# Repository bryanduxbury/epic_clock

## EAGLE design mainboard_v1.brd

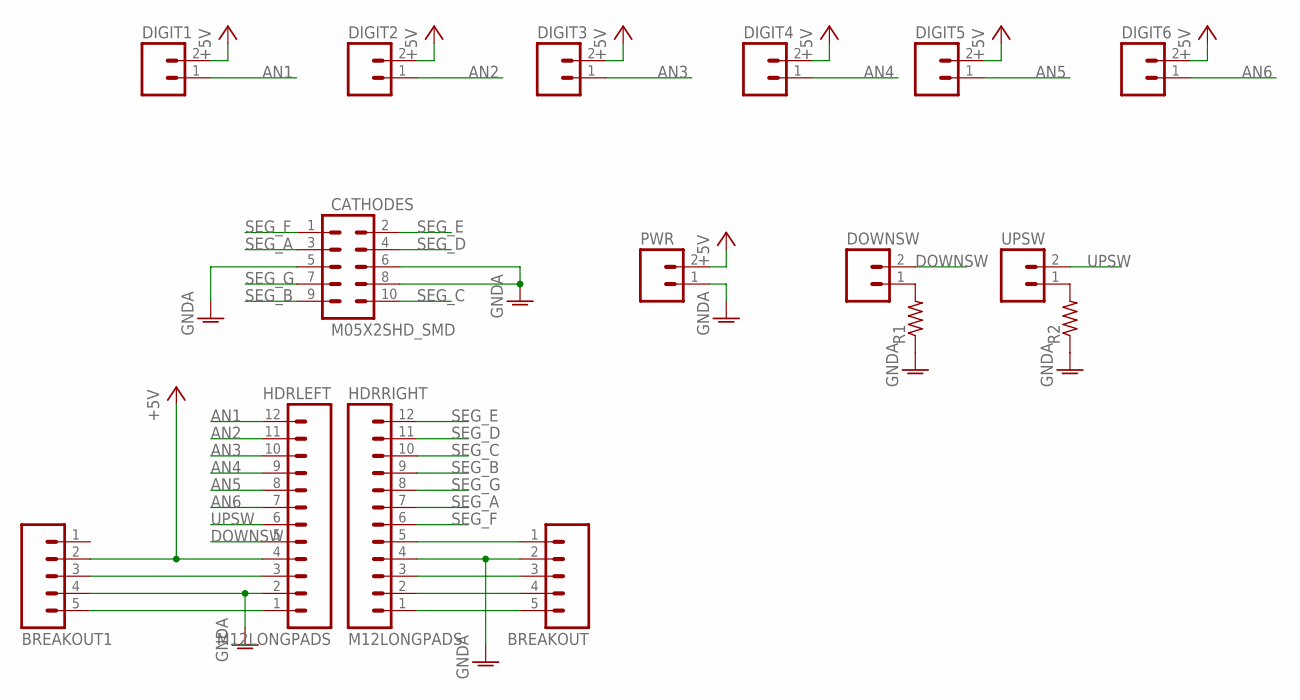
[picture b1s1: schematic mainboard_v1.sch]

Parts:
BREAKOUT, BREAKOUT1: M05; 05P
CATHODES: M05X2SHD_SMD; 2X5-SHROUDED_SMD
DIGIT1, DIGIT2, DIGIT3, DIGIT4, DIGIT5, DIGIT6: M02; 02P
DOWNSW: M02; 02P
HDRLEFT: M12LONGPADS; 1X12_LONGPADS
HDRRIGHT: M12LONGPADS; 1X12_LONGPADS
PWR: M02; 02P
R1, R2: R-US_M0805; M0805
UPSW: M02; 02P

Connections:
+5V: BREAKOUT1.2, DIGIT1.2, DIGIT2.2, DIGIT3.2, DIGIT4.2, DIGIT5.2, DIGIT6.2, HDRLEFT.4, PWR.2
AN1: DIGIT1.1, HDRLEFT.12
AN2: DIGIT2.1, HDRLEFT.11
AN3: DIGIT3.1, HDRLEFT.10
AN4: DIGIT4.1, HDRLEFT.9
AN5: DIGIT5.1, HDRLEFT.8
AN6: DIGIT6.1, HDRLEFT.7
DOWNSW: DOWNSW.2, HDRLEFT.5
GNDA: BREAKOUT.2, BREAKOUT1.4, CATHODES.5, CATHODES.6, CATHODES.8, HDRLEFT.2, HDRRIGHT.4, PWR.1, R1.1, R2.1
unnamed: DOWNSW.1, R1.2
unnamed: BREAKOUT.1, HDRRIGHT.5
unnamed: R2.2, UPSW.1
unnamed: BREAKOUT.3, HDRRIGHT.3
unnamed: BREAKOUT.4, HDRRIGHT.2
unnamed: BREAKOUT.5, HDRRIGHT.1
unnamed: BREAKOUT1.5, HDRLEFT.1
unnamed: BREAKOUT1.3, HDRLEFT.3
SEG_A: CATHODES.3, HDRRIGHT.7
SEG_B: CATHODES.9, HDRRIGHT.9
SEG_C: CATHODES.10, HDRRIGHT.10
SEG_D: CATHODES.4, HDRRIGHT.11
SEG_E: CATHODES.2, HDRRIGHT.12
SEG_F: CATHODES.1, HDRRIGHT.6
SEG_G: CATHODES.7, HDRRIGHT.8
UPSW: HDRLEFT.6, UPSW.2

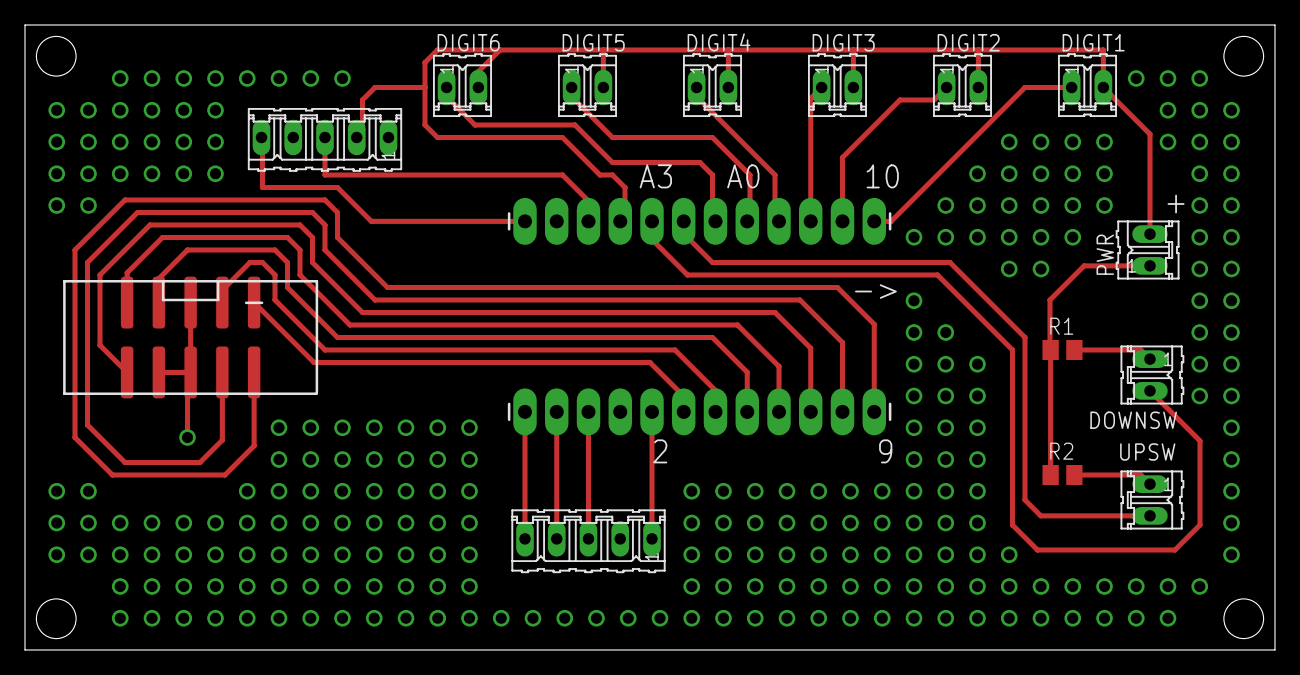
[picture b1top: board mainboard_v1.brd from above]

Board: 2 copper layers, 100.0 x 50.0 mm, 16 parts (0 on the bottom side), 25 nets.

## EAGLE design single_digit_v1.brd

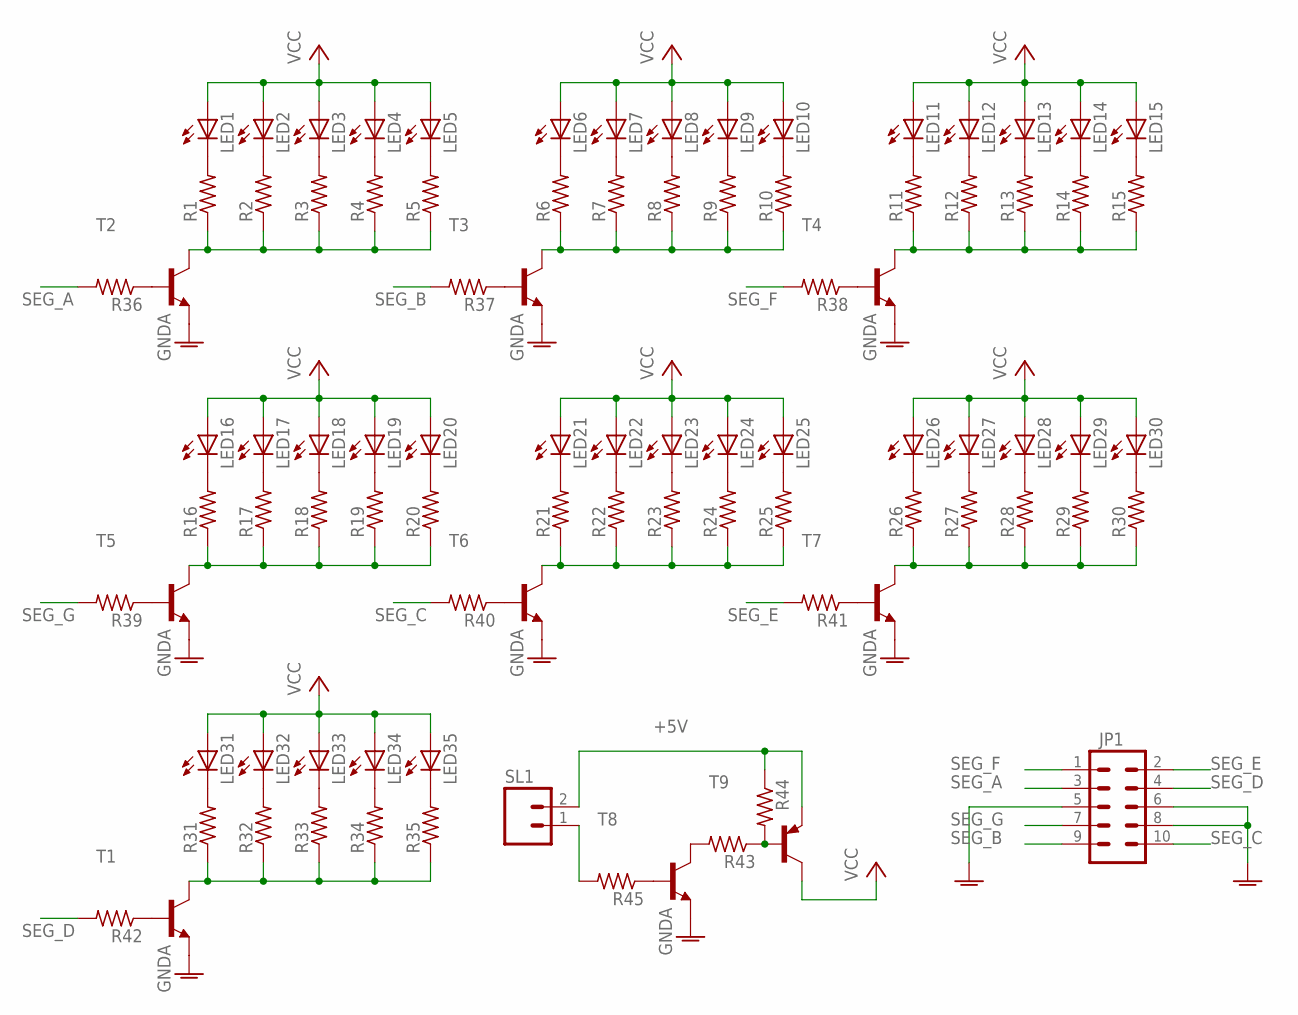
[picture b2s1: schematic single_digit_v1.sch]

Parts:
JP1: M05X2SHD_SMD; 2X5-SHROUDED_SMD
LED1, LED2, LED3, LED4, LED5, LED6, LED7, LED8, LED9, LED10, LED11, LED12, LED13, LED14, LED15, LED16, LED17, LED18, LED19, LED20, LED21, LED22, LED23, LED24, LED25, LED26, LED27, LED28, LED29, LED30, LED31, LED32, LED33, LED34, LED35: LED5MM
R1, R2, R3, R4, R5, R6, R7, R8, R9, R10, R11, R12, R13, R14, R15, R16, R17, R18, R19, R20, R21, R22, R23, R24, R25, R26, R27, R28, R29, R30, R31, R32, R33, R34, R35, R36, R37, R38, R39, R40, R41, R42, R43, R44, R45: R-US_M0805; M0805
SL1: M02; 02P
T1, T2, T3, T4, T5, T6, T7, T8: MMBT2222ALT1-NPN-SOT23-BEC; SOT23-BEC
T9: MMBT2907ALT1-PNP-SOT23-BEC; SOT23-BEC

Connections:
+5V: R44.1, SL1.2, T9.E
GNDA: JP1.5, JP1.6, JP1.8, T1.E, T2.E, T3.E, T4.E, T5.E, T6.E, T7.E, T8.E
unnamed: LED1.K (C), R1.2
unnamed: LED2.K (C), R2.2
unnamed: LED3.K (C), R3.2
unnamed: LED4.K (C), R4.2
unnamed: LED5.K (C), R5.2
unnamed: LED6.K (C), R6.2
unnamed: LED7.K (C), R7.2
unnamed: LED8.K (C), R8.2
unnamed: LED9.K (C), R9.2
unnamed: LED10.K (C), R10.2
unnamed: LED11.K (C), R11.2
unnamed: LED12.K (C), R12.2
unnamed: LED13.K (C), R13.2
unnamed: LED14.K (C), R14.2
unnamed: LED15.K (C), R15.2
unnamed: LED16.K (C), R16.2
unnamed: LED17.K (C), R17.2
unnamed: LED18.K (C), R18.2
unnamed: LED19.K (C), R19.2
unnamed: LED20.K (C), R20.2
unnamed: LED21.K (C), R21.2
unnamed: LED22.K (C), R22.2
unnamed: LED23.K (C), R23.2
unnamed: LED24.K (C), R24.2
unnamed: LED25.K (C), R25.2
unnamed: LED26.K (C), R26.2
unnamed: LED27.K (C), R27.2
unnamed: LED28.K (C), R28.2
unnamed: LED29.K (C), R29.2
unnamed: LED30.K (C), R30.2
unnamed: LED31.K (C), R31.2
unnamed: LED32.K (C), R32.2
unnamed: LED33.K (C), R33.2
unnamed: LED34.K (C), R34.2
unnamed: LED35.K (C), R35.2
unnamed: R1.1, R2.1, R3.1, R4.1, R5.1, T2.C
unnamed: R6.1, R7.1, R8.1, R9.1, R10.1, T3.C
unnamed: R11.1, R12.1, R13.1, R14.1, R15.1, T4.C
unnamed: R36.1, T2.B
unnamed: R37.1, T3.B
unnamed: R38.1, T4.B
unnamed: R39.1, T5.B
unnamed: R16.1, R17.1, R18.1, R19.1, R20.1, T5.C
unnamed: R21.1, R22.1, R23.1, R24.1, R25.1, T6.C
unnamed: R26.1, R27.1, R28.1, R29.1, R30.1, T7.C
unnamed: R40.1, T6.B
unnamed: R31.1, R32.1, R33.1, R34.1, R35.1, T1.C
unnamed: R41.1, T7.B
unnamed: R42.1, T1.B
unnamed: R43.2, T8.C
unnamed: R43.1, R44.2, T9.B
unnamed: R45.1, T8.B
unnamed: R45.2, SL1.1
SEG_A: JP1.3, R36.2
SEG_B: JP1.9, R37.2
SEG_C: JP1.10, R40.2
SEG_D: JP1.4, R42.2
SEG_E: JP1.2, R41.2
SEG_F: JP1.1, R38.2
SEG_G: JP1.7, R39.2
VCC: LED1.A, LED2.A, LED3.A, LED4.A, LED5.A, LED6.A, LED7.A, LED8.A, LED9.A, LED10.A, LED11.A, LED12.A, LED13.A, LED14.A, LED15.A, LED16.A, LED17.A, LED18.A, LED19.A, LED20.A, LED21.A, LED22.A, LED23.A, LED24.A, LED25.A, LED26.A, LED27.A, LED28.A, LED29.A, LED30.A, LED31.A, LED32.A, LED33.A, LED34.A, LED35.A, T9.C

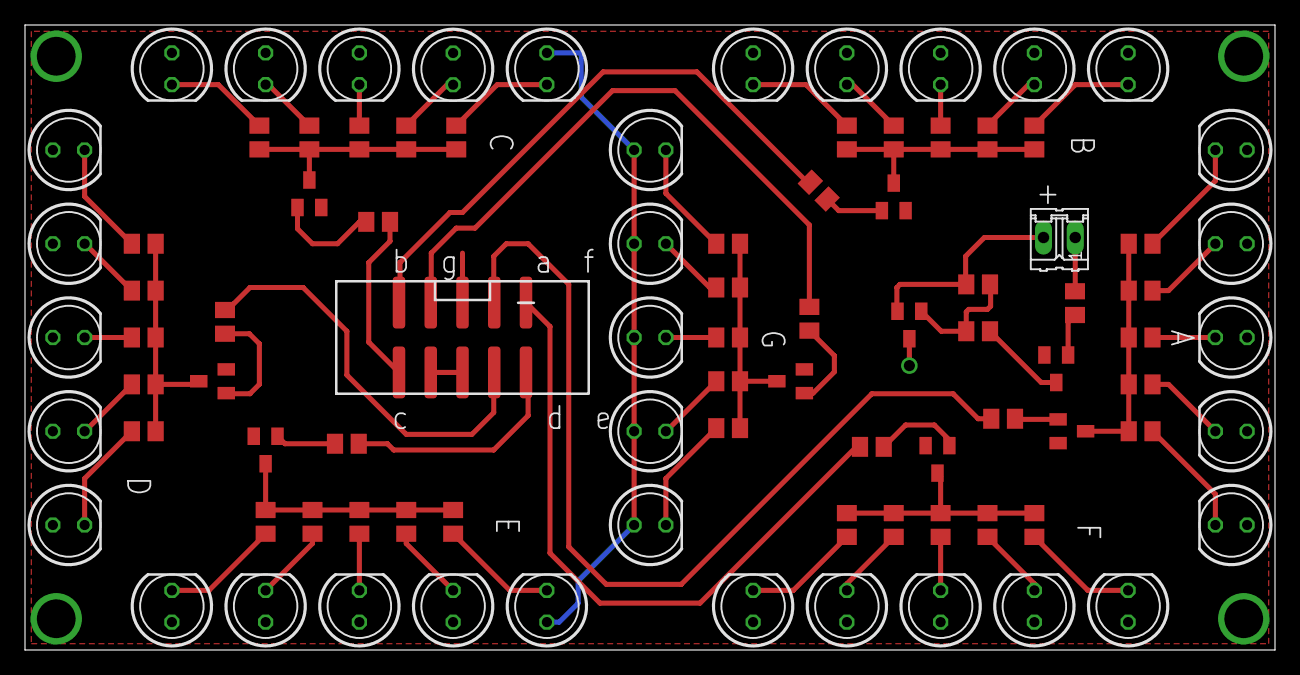
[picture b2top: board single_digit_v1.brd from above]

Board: 2 copper layers, 100.0 x 50.0 mm, 91 parts (0 on the bottom side), 63 nets.

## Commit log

2014-08-05 init commit
2014-08-11 ready for production
2014-08-11 add bunch of eagle gerber formats to gitignore
2014-08-21 add labels to boards to aid in, you know, using them
2014-08-21 simple sketch to try turning on/off segments
2014-08-21 WIP of actual firmware w/timer based strobing
2014-08-25 draft of scadfile for the enclosure
2014-08-25 oops, tester had a bug
2015-08-13 outstanding work

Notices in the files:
parts and their libraries:
SparkFun-Connectors: Licensing: Creative Commons ShareAlike 4.0 International - https://creativecommons.org/licenses/by-sa/4.0
